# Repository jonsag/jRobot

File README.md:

# jRobot

My take on B-ROBOT found at https://github.com/jjrobots/B-ROBOT

## WiFI Remote

[https://play.google.com/store/apps/details?id=com.realwox.wifirccontroller&hl=en_US&gl=US](https://play.google.com/store/apps/details?id=com.realwox.wifirccontroller&hl=en_US&gl=US)
[https://play.google.com/store/apps/details?id=com.lacour.vincent.wificaresp8266&hl=en_US&gl=US](https://play.google.com/store/apps/details?id=com.lacour.vincent.wificaresp8266&hl=en_US&gl=US)

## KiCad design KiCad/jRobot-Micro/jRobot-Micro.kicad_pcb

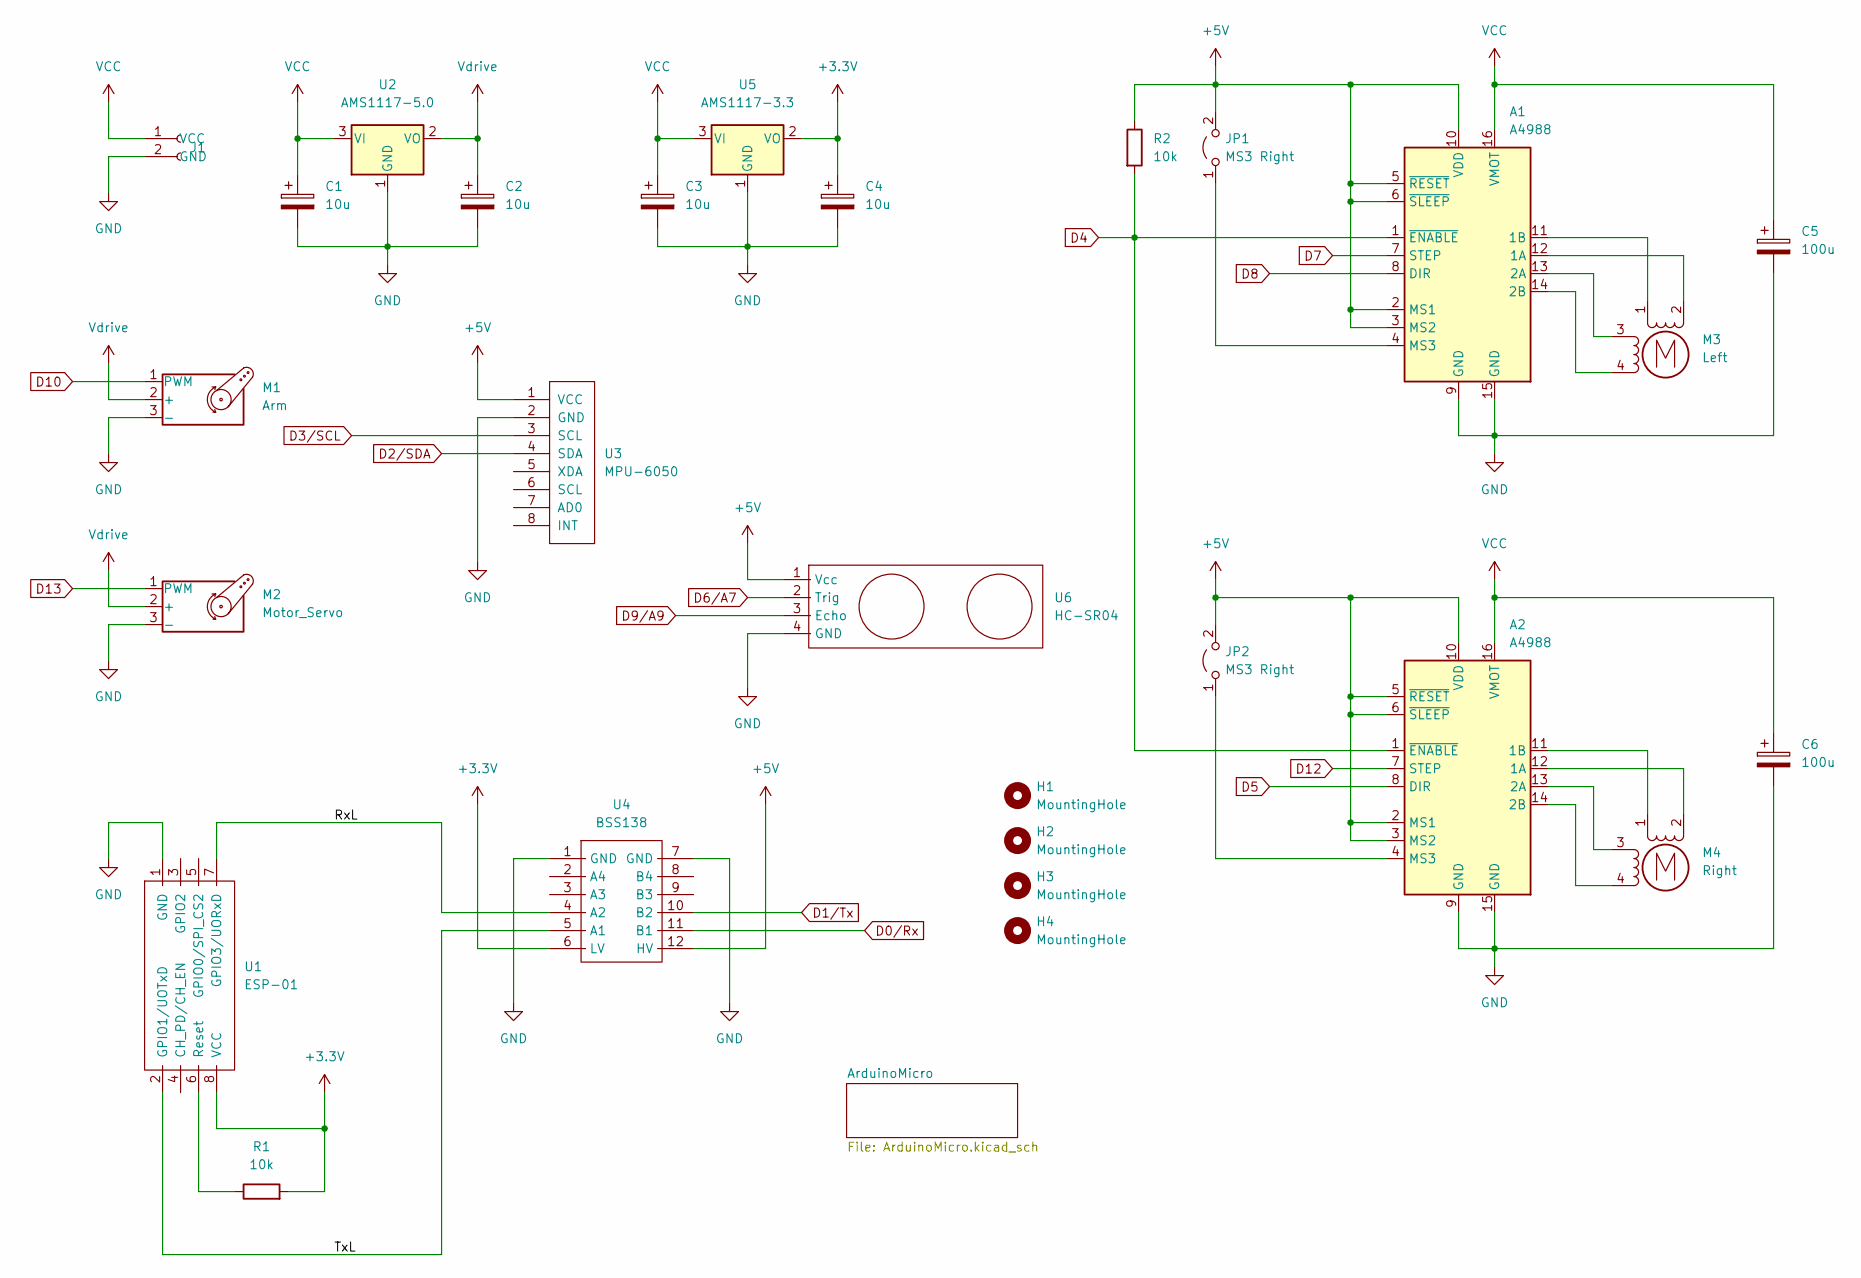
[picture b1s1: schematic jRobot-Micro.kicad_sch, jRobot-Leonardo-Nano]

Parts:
A1, A2: A4988; Pololu_Breakout-16_15.2x20.3mm_large
C1, C2, C3, C4: 10u; CP_Radial_D5.0mm_P2.00mm_larger
C5, C6: 100u; CP_Radial_D5.0mm_P2.00mm_larger
H1, H2, H3, H4: MountingHole; MountingHole_3.2mm_M3
J1: 2-pin_power_input_header
JP1, JP2: MS3 Right; Jumper_1x02_P2.54mm_large
M1: Arm; 3-pin JST Servo
M2: Motor_Servo
M3: Left; PhoenixPCB_2-Pole_Stepper_Connector
M4: Right; PhoenixPCB_2-Pole_Stepper_Connector
R1, R2: 10k; R_Axial_DIN0207_L6.3mm_D2.5mm_P10.16mm_Horizontal_large
U1: ESP-01; ESP-01_w_pin_socket_large
U2: AMS1117-5.0; SOT-223-3_TabPin2
U3: MPU-6050; GY-521_MPU6050_w_header_large
U4: BSS138; 4-channel_I2C_level_shifter_BSS138_large
U5: AMS1117-3.3; SOT-223-3_TabPin2
U6: HC-SR04; 4-pin JST HC-SR04 Sonar

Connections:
+3.3V: C4.1, R1.2, U1.8 (VCC), U4.6 (LV), U5.2 (VO); also elsewhere on the board
+5V: A1.2 (MS1), A1.3 (MS2), A1.5 (~RESET), A1.6 (~SLEEP), A1.10 (VDD), A2.2 (MS1), A2.3 (MS2), A2.5 (~RESET), A2.6 (~SLEEP), A2.10 (VDD), JP1.2 (B), JP2.2 (B), R2.1, U3.1 (VCC), U4.12 (HV), U6.1 (Vcc); also elsewhere on the board
/RxL: U1.7 (GPIO3/UORxD), U4.4 (A2)
/TxL: U1.2 (GPIO1/UOTxD), U4.5 (A1)
D0/Rx: U4.11 (B1); also elsewhere on the board
D1/Tx: U4.10 (B2); also elsewhere on the board
D2/SDA: U3.4 (SDA); also elsewhere on the board
D3/SCL: U3.3 (SCL); also elsewhere on the board
D4: A1.1 (~ENABLE), A2.1 (~ENABLE), R2.2
D5: A2.8 (DIR); also elsewhere on the board
D6/A7: U6.2 (Trig); also elsewhere on the board
D7: A1.7 (STEP); also elsewhere on the board
D8: A1.8 (DIR)
D9/A9: U6.3 (Echo); also elsewhere on the board
D10: M1.1 (PWM)
D12: A2.7 (STEP)
GND: A1.9 (GND), A1.15 (GND), A2.9 (GND), A2.15 (GND), C1.2, C2.2, C3.2, C4.2, C5.2, C6.2, J1.2 (GND), M1.3 (-), M2.3 (-), U1.1 (GND), U2.1 (GND), U3.2 (GND), U4.1 (GND), U4.7 (GND), U5.1 (GND), U6.4 (GND); also elsewhere on the board
unnamed: A1.4 (MS3), JP1.1 (A)
unnamed: A1.11 (1B), M3.1
unnamed: A1.12 (1A), M3.2 (-)
unnamed: A1.13 (2A), M3.3
unnamed: A1.14 (2B), M3.4
unnamed: A2.4 (MS3), JP2.1 (A)
unnamed: A2.11 (1B), M4.1
unnamed: A2.12 (1A), M4.2 (-)
unnamed: A2.13 (2A), M4.3
unnamed: A2.14 (2B), M4.4
unnamed: R1.1, U1.6 (Reset)
VCC: A1.16 (VMOT), A2.16 (VMOT), C1.1, C3.1, C5.1, C6.1, J1.1 (VCC), U2.3 (VI), U5.3 (VI); also elsewhere on the board
Vdrive: C2.1, M1.2 (+), M2.2 (+), U2.2 (VO)

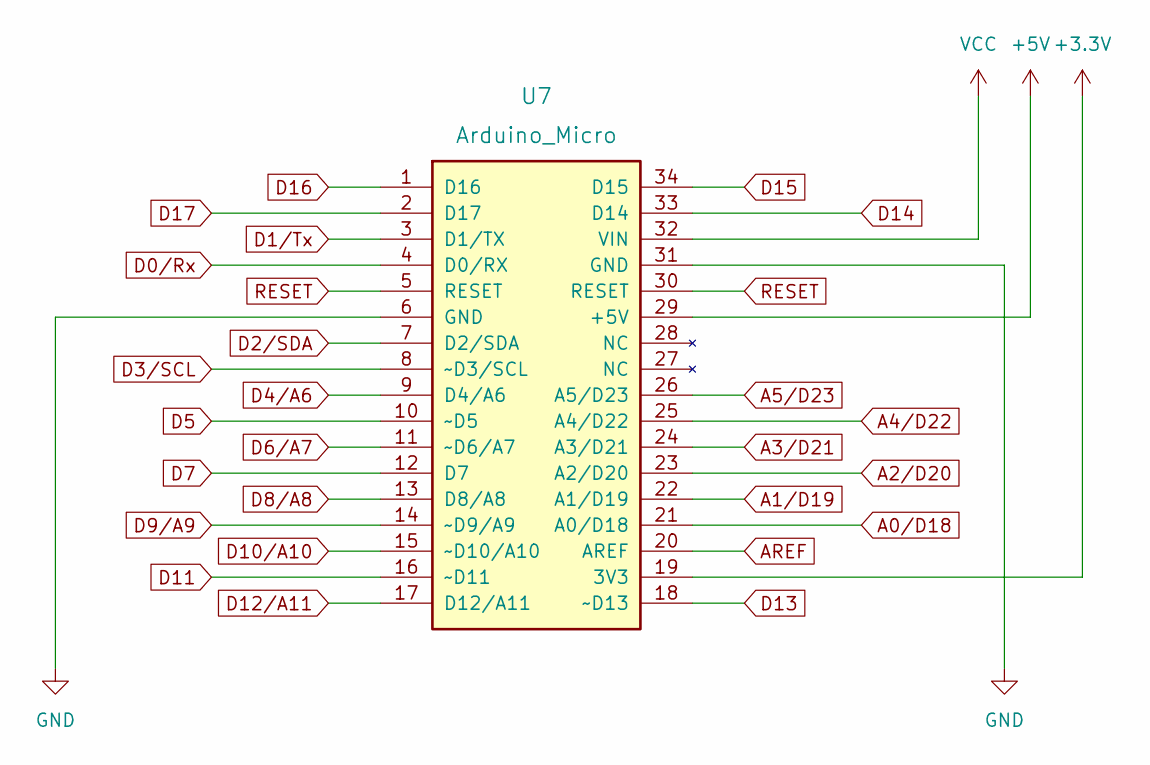
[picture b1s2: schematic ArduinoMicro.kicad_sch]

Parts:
U7: Arduino_Micro; Arduino_Micro large

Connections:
+3.3V: U7.19 (3V3); also elsewhere on the board
+5V: U7.29 (+5V); also elsewhere on the board
A0/D18: U7.21 (A0/D18)
A1/D19: U7.22 (A1/D19)
A2/D20: U7.23 (A2/D20)
A3/D21: U7.24 (A3/D21)
A4/D22: U7.25 (A4/D22)
A5/D23: U7.26 (A5/D23)
AREF: U7.20 (AREF)
D0/Rx: U7.4 (D0/RX); also elsewhere on the board
D1/Tx: U7.3 (D1/TX); also elsewhere on the board
D2/SDA: U7.7 (D2/SDA); also elsewhere on the board
D3/SCL: U7.8 (~D3/SCL); also elsewhere on the board
D4/A6: U7.9 (D4/A6)
D5: U7.10 (~D5); also elsewhere on the board
D6/A7: U7.11 (~D6/A7); also elsewhere on the board
D7: U7.12 (D7); also elsewhere on the board
D8/A8: U7.13 (D8/A8)
D9/A9: U7.14 (~D9/A9); also elsewhere on the board
D10/A10: U7.15 (~D10/A10)
D11: U7.16 (~D11)
D12/A11: U7.17 (D12/A11)
D13: U7.18 (~D13)
D14: U7.33 (D14)
D15: U7.34 (D15)
D16: U7.1 (D16)
D17: U7.2 (D17)
GND: U7.6 (GND), U7.31 (GND); also elsewhere on the board
RESET: U7.5 (RESET), U7.30 (RESET)
VCC: U7.32 (VIN); also elsewhere on the board

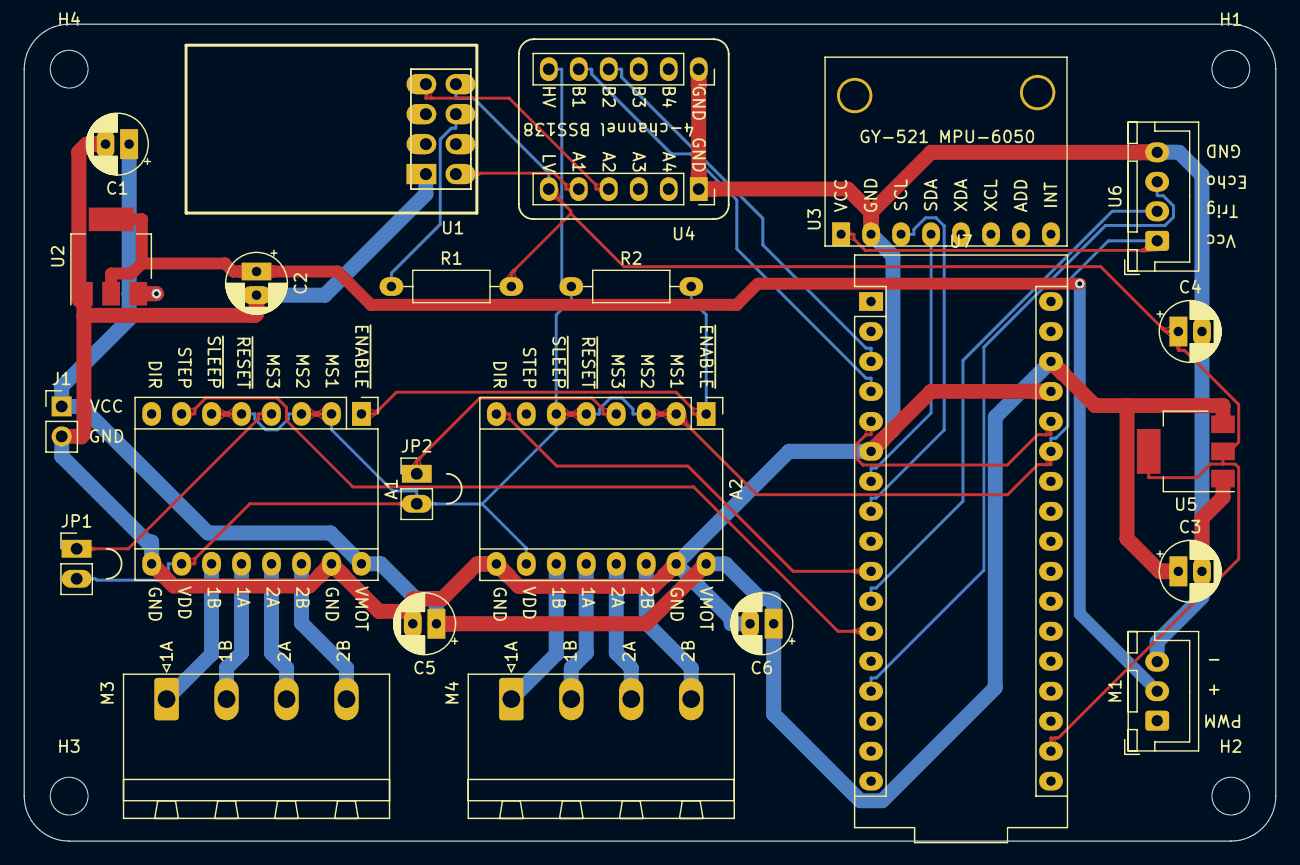
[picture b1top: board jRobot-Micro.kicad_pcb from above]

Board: 2 copper layers, 106.0 x 69.2 mm, 27 parts (0 on the bottom side), 28 nets.

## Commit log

2022-12-18 leonardo
2022-12-18 prettyfying
2022-12-20 arduino micro
2022-12-20 moved pin definitions to config
